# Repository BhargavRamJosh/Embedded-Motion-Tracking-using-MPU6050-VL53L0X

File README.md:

# 🚀 IMU-ToF Sensor Fusion for Tilt and Displacement Measurement

## 📌 Overview
This project implements a **real-time motion tracking system** using:
- **MPU6050 (IMU)** for tilt angle estimation  
- **VL53L0X (ToF Sensor)** for distance measurement  
- **ESP32** for processing  

The system calculates:
- 📐 Tilt Angle (degrees)  
- 📏 Height Difference (mm)  
- 📊 Linear Displacement (mm)  

---

## 🎯 Features
- Real-time tilt estimation using **sensor fusion**
- Complementary filter for **noise reduction & stability**
- Trigonometric height calculation
- Accurate distance measurement using ToF sensor
- Lightweight and efficient embedded implementation

---

## 🖼️ Project Images

### 🔹 Hardware Setup

### 🔹 Serial Output

### 🔹 Final Result

---

## 🧠 Working Principle

### 1. Sensor Fusion (Complementary Filter)

```cpp
angle = alpha * (angle + gyroRate * dt) + (1 - alpha) * accelAngle;

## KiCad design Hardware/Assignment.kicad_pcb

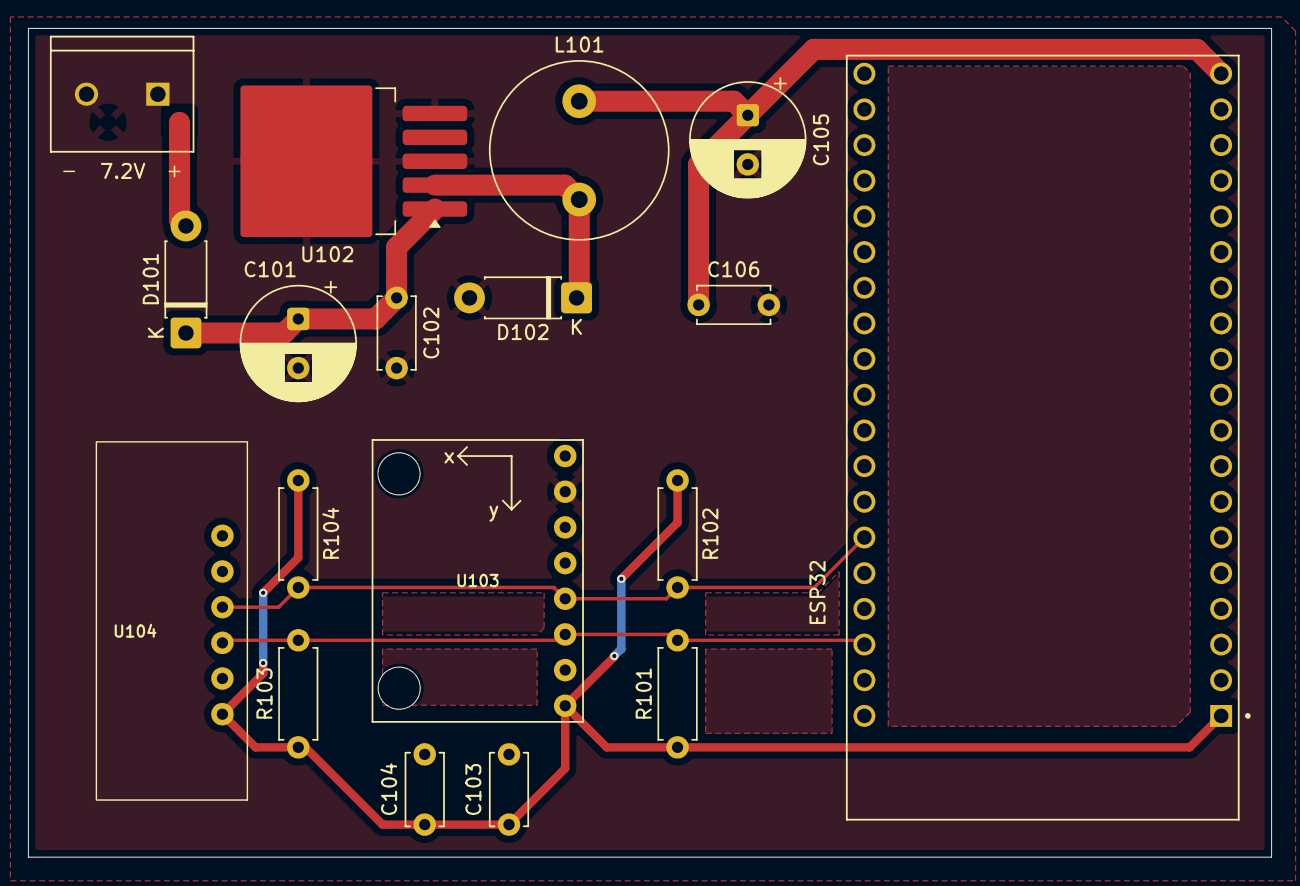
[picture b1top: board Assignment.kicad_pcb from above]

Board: 2 copper layers, 88.5 x 59.0 mm, 18 parts (0 on the bottom side), 10 nets.

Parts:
7.2V: Screw_Terminal_01x02; TE_282837-2
C101: 100uF; CP_Radial_D8.0mm_P3.50mm
C102, C103, C104, C106: 0.1uF; C_Disc_D5.0mm_W2.5mm_P5.00mm
C105: 220uF; CP_Radial_D8.0mm_P3.50mm
D101, D102: SS14; D_DO-41_SOD81_P7.62mm_Horizontal
ESP32: ESP32-DEVKITC-32D; MODULE_ESP32-DEVKITC-32D
L101: 33uH; L_Radial_D12.5mm_P7.00mm_Fastron_09HCP
R101, R102, R103, R104: 4.7k; R_Axial_DIN0207_L6.3mm_D2.5mm_P7.62mm_Horizontal
U102: LM2596S-5; TO-263-5_TabPin3
U103: GY-521
U104: VL53LX0; GY-521

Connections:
/3.3V: C103.1, C104.1, ESP32.J2-1 (3V3), R101.1, R102.1, R103.1, R104.1, U103.VCC, U104.VCC
/SCL: ESP32.J3-3 (IO22), R101.2, R103.2, U103.SCL, U104.SCL
/SDA: ESP32.J3-6 (IO21), R102.2, R104.2, U103.SDA, U104.SDA
/VIN: C105.1, C106.1, ESP32.J2-19 (EXT_5V), L101.2
GND: 7.2V.2, C101.2, C102.2, C105.2, C106.2, D102.2 (A), U102.3 (GND), U102.5 (~ON/OFF), U103.ADO
unnamed: C103.2, U103.GND
unnamed: C104.2, U104.GND
unnamed: 7.2V.1, D101.2 (A)
unnamed: C101.1, C102.1, D101.1 (K), U102.1 (VIN)
unnamed: D102.1 (K), L101.1, U102.2 (OUT)

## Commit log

2026-04-21 Revise README for IMU-ToF Sensor Fusion project
    Updated project title and added detailed overview, features, images, and working principle sections.
